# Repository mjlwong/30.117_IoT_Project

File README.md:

# 30.117 Wireless Comm. & IoT Project

## Introduction

This IoT Project is a humidity and temperature sensor, primarily for use in camera dryboxes. It may also be used for any closed area that needs its humidity monitored, such as 3D printer filament dryers. The project consists of an ESP32C6 DevkitC-1 as its main microcontroller, a SHT31 Humidity and Temperature sensor, and a 3D printed casing to hold the circuitry and a portable power source. ESP Rainmaker is used as the main cloud service for this IoT project. 

## Directories

* `.devcontainer`
* `.vscode`
* `CAD_Files` - Files containing the Fusion 360 model of the holder
* `Docs` - Files containing the dimensions, circuit diagram and user guides of the project
* `main` - Main folder containing C file for firmware, CMakeList, and configuration file for the menu
    * `/CMakeLists.txt` - CMake file for main folder
    * `/idf_component.yml` - YML file detailing required dependencies for this project
    * `/Kconfig.projbuild` - Custom configuration file for easy troubleshooting
    * `/main.c` - Main C file containing firmware code for the ESP32C6
* `.clangd`
* `CMakeLists.txt` - CMake file for overall project
* `dependencies.lock`
* `partitions_4mb_optmimised.csv` - CSV file to detail how the ESP32C6 flash memory will be partitioned
* `sdkconfig.defaults` - Configuration file for project
* `sdkconfig.defaults.esp32` - Configuration file specific to ESP32 boards
* `sdkconfig.defaults.esp32c6` - Configuration file specific to ESP32C6 boards

## Dependencies

The following ESP-IDF components are required for this project:

* [ESP RainMaker Agent Component](https://components.espressif.com/components/espressif/esp_rainmaker/versions/1.12.1/readme)
* [RainMaker App Network Component](https://components.espressif.com/components/espressif/rmaker_app_network/versions/1.4.0/readme)
* [RainMaker App Insights Component](https://components.espressif.com/components/espressif/rmaker_app_insights/versions/1.0.0/readme)
* [esp-idf-lib/sht3x](https://components.espressif.com/components/esp-idf-lib/sht3x/versions/1.0.8/readme)

## User Guide

* [Getting Started](Docs/GettingStarted.md)
* [Configuring](Docs/Configuring.md)
* [Hardware](Docs/Hardware.md)
* [Normal Usage](Docs/NormalUsage.md)

## Known issues

The ESP Rainmaker App on IOS does not have a UI type for one of the components. To fix this, go to `main/main.c`, line 218, and change `ESP_RMAKER_UI_TRIGGER` to `ESP_RMAKER_UI_TOGGLE`.

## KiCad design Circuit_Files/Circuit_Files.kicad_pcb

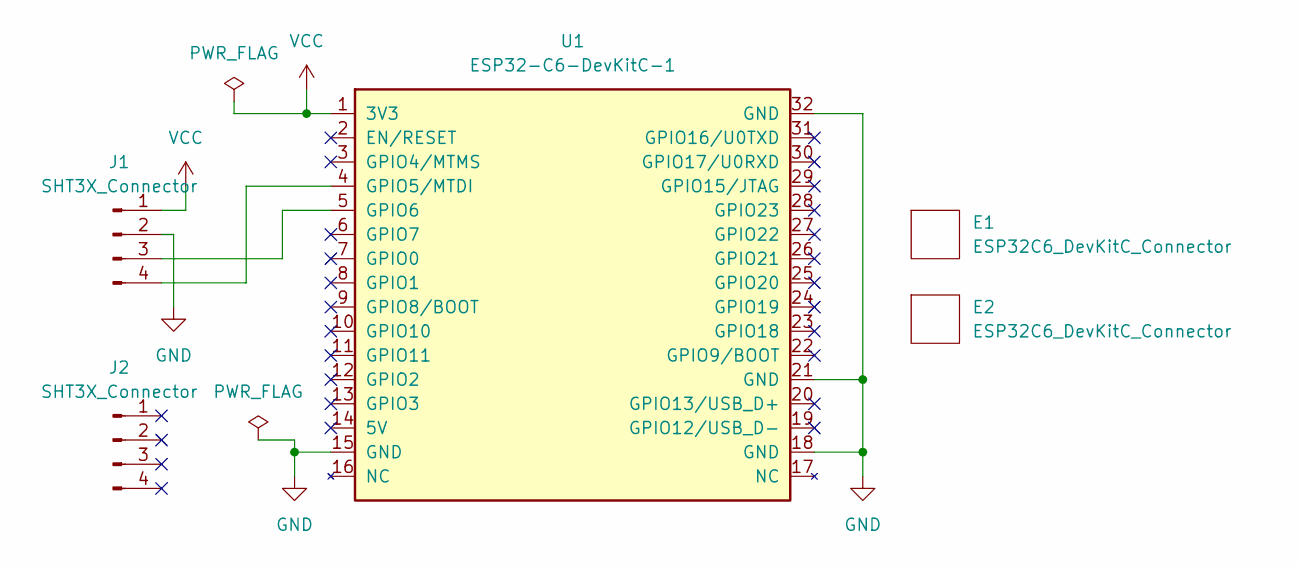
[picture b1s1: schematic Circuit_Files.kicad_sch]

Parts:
E1, E2: ESP32C6_DevKitC_Connector; EmptyFootprint
J1, J2: SHT3X_Connector; PinSocket_1x04_P2.54mm_Vertical
U1: ESP32-C6-DevKitC-1

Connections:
GND: J1.2, U1.15 (GND), U1.18 (GND), U1.21 (GND), U1.32 (GND)
unnamed: J1.3, U1.5 (GPIO6)
unnamed: J1.4, U1.4 (GPIO5/MTDI)
VCC: J1.1, U1.1 (3V3)

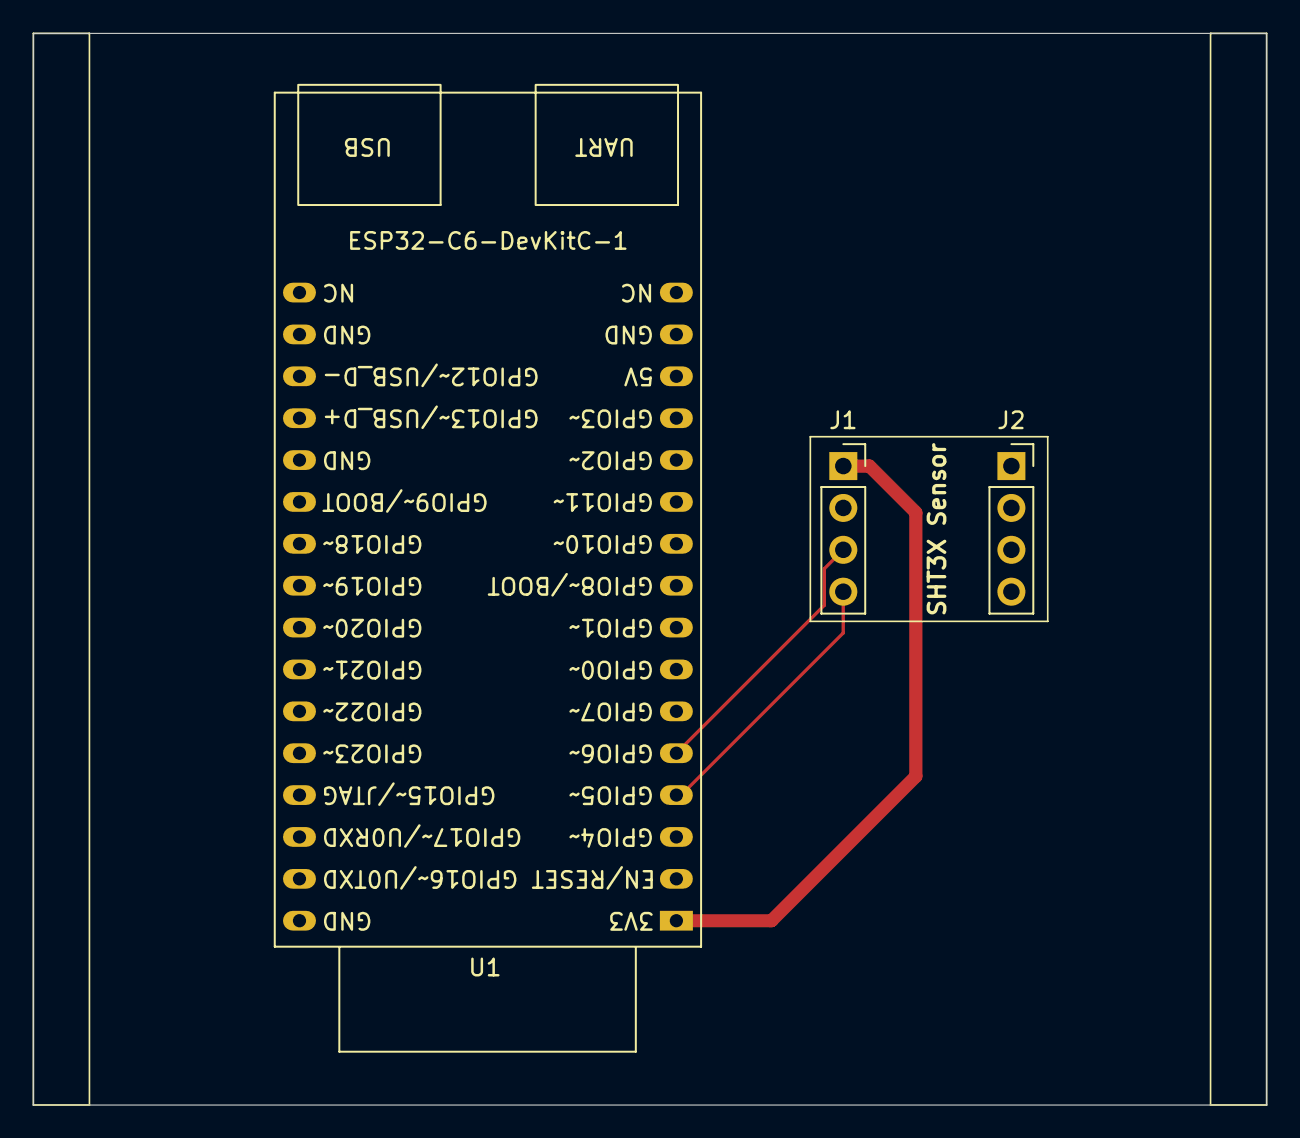
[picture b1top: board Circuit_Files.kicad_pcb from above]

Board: 2 copper layers, 74.8 x 65.0 mm, 5 parts (0 on the bottom side), 4 nets.

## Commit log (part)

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2026-03-04 Added additional config files, readme, and code for the main function
2026-03-05 Added partition table and modified main file with rainmaker and sensor code
2026-03-07 Added Config Files for the project
2026-03-07 First working draft of code that updates IoT cloud date from sensor
2026-03-09 Final draft of working code
2026-03-11 Next final draft of working code
2026-03-13 Final final code for the project
2026-03-16 Modified configuration file and menu to be more intuitive
2026-03-16 Minor change to kconfig.projbuild
2026-03-18 Added Config option to change the time interval of updating the cloud data
2026-03-18 Minor change in main file comments
2026-03-20 Modified README.md file, added CAD and circuit schematic files
2026-03-20 Completed some of the user guides
2026-03-20 Modified user guides
2026-03-20 Modified image file formats
2026-03-21 Added more tutorials
2026-03-21 Written more tutorials for code documentation
2026-03-22 Added a flowchart for the firmware programme
2026-03-22 Minor change to tutorial
2026-03-22 Modified flowchart for firmware programme
2026-03-22 Modified tutorials in project
2026-03-23 Refined the flowchart further
2026-03-23 Added correct pictures for documentation
2026-03-24 Made minor change to main file
2026-03-26 Made small adjustment to main file
2026-04-28 Modified CMakeList file
2026-04-28 Undid last edit
2026-05-17 Added circuit files for repo, corrected dimension for holder orthographic drawing
2026-06-08 Humidity and Temperature values are averaged out before uploaded, added db file for JLCPCB
2026-06-08 Fixed minor error; forgot to clear summed values
